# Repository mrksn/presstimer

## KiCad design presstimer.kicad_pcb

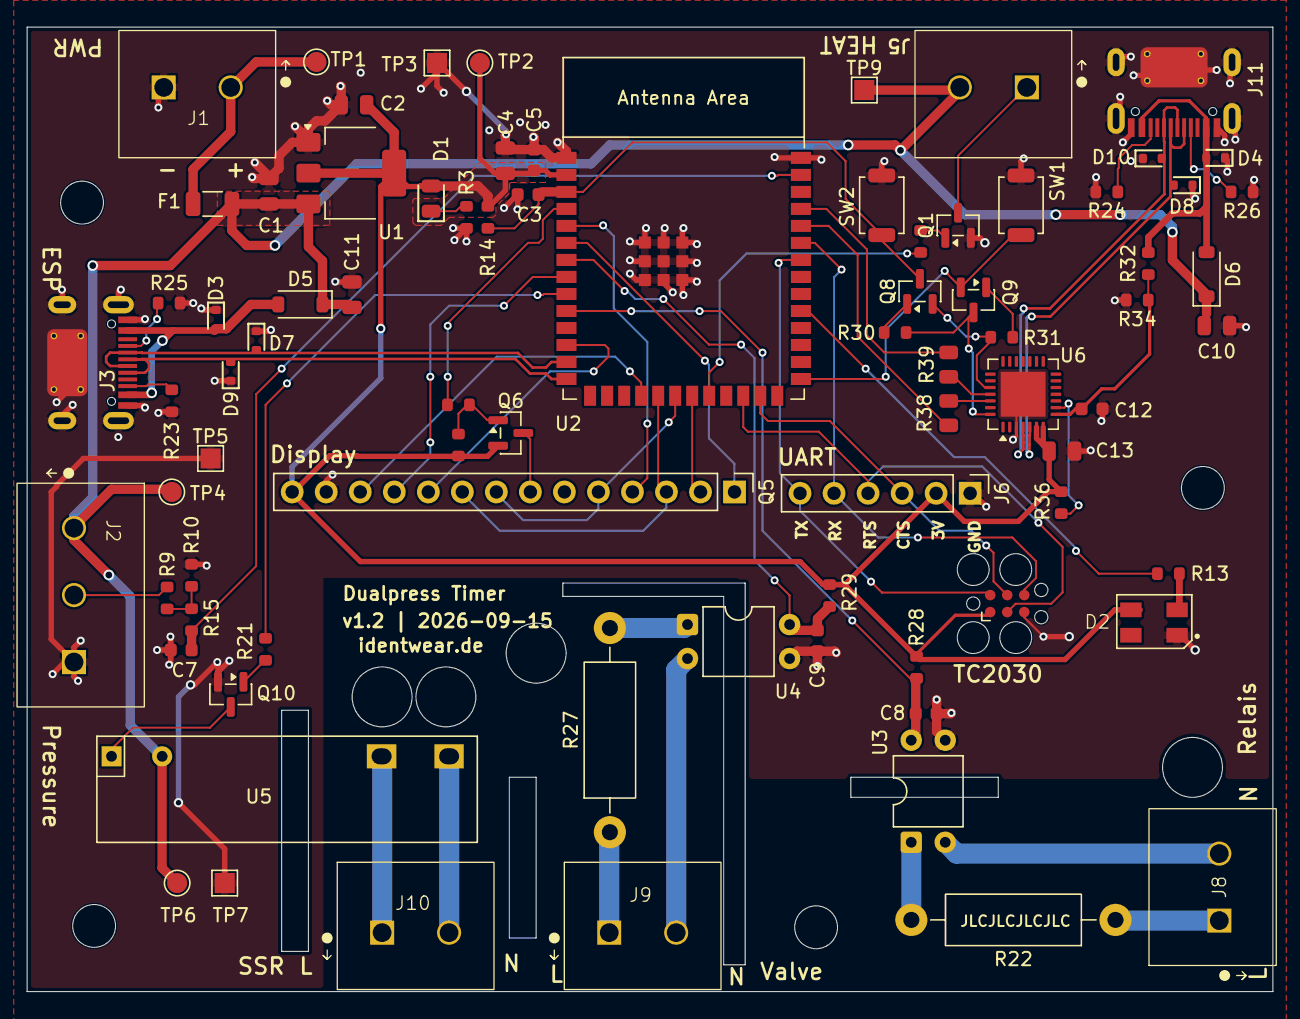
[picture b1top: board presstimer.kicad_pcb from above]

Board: 4 copper layers, 93.0 x 72.0 mm, 84 parts (0 on the bottom side), 63 nets.

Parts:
C1, C2: 1uF; C_0805
C3, C12: 1uF; C_0603
C4, C13: 10uF; C_0805
C5, C7, C8, C9: 100nF; C_0603
C10, C11: 22uF; C_0805
D1: LED; D_0805
D2: SK6812MINI; SK6812MINI--HS-012_3.7x3.5mm
D3, D4, D7, D8, D9, D10: LESD5D5.0CT1G; D_SOD-523
D5, D6: 1N5819HW-7-F; D_SOD-123
F1: Polyfuse; 1206L300SL16ARG
H1, H2, H3, H4: MountingHole; MountingHole_3.2mm_M3
J1, J5, J8, J9, J10: Screw_Terminal_01x02; DG305-5.0-02P-12-00A(H)
J2: Screw_Terminal_01x03; DG305-5.0-03P-12-00A(H)
J3, J11: Connector, USB-TYPE-C-16P; TYPE-C-SMD_HX-TYPE-C-16PIN
J4: Conn_ARM_SWD_TagConnect_TC2030; Tag-Connect_TC2030-IDC-FP_2x03_P1.27mm_Vertical
J6: Conn_01x06_Pin; PinHeader_1x06_P2.54mm_Vertical
Q1, Q8, Q9, Q10: L8050QLT1G; SOT-23
Q5: Display 2.8" TFT LCD Touch ILI9431 SPI; PinHeader_1x14_P2.54mm_Vertical
Q6: AO3401A; SOT-23
R1, R3, R15, R21, R36: 1k; R_0603
R9, R14, R30, R31: 10k; R_0603
R10: 15k; R_0603
R13: 330; R_0603
R16: 100; R_0603
R17: 100k; R_0603
R22, R27: 300k; R_Axial_DIN0411_L9.9mm_D3.6mm_P15.24mm_Horizontal
R23, R24, R25, R26: 5k1; R_0603
R28, R29: 47k; R_0603
R32: 22k1; R_0603
R34: 47k5; R_0603
R38, R39: 0; R_0805
SW1, SW2: SW_Push; SW_SPST_TS-1088-xR025
TP1, TP2, TP4, TP6: TestPoint; TestPoint_Pad_D1.5mm
TP3, TP5, TP7, TP9: TestPoint; TestPoint_Pad_1.5x1.5mm
U1: AP7361C-33ER; SOT-223R
U2: ESP32-S3-WROOM-1
U3, U4: SFH620A-3X001; DIP-4_W7.62mm
U5: SSR-41FDA; SSR-41FDD
U6: CP2102N-Axx-xQFN28; QFN-28-1EP_5x5mm_P0.5mm_EP3.35x3.35mm

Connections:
+3V3: C2.1, C4.1, C5.1, C13.1, D1.2 (A), D2.3 (VDD), J4.1 (VCC), J6.2, Q5.14 (VCC), Q6.2 (S), R14.2, R17.1, R28.1, R29.1, R36.1, TP2.1 (1_1), U1.2 (OUT), U1.4 (OUT), U2.2 (3V3), U6.6 (VDD), U6.7 (VREGIN)
+5V: C1.1, C10.1, C11.1, D5.1 (K), D6.1 (K), F1.2, J2.1, J5.2, TP4.1 (1_1), TP6.1 (1_1), TP9.1 (1_1), U1.3 (IN), U5.3 (+)
/Connections/SENSE_RELAY1: J8.1, R22.1
/Connections/SENSE_RELAY2: J8.2, U3.2
/Connections/SENSE_SOLENOID1: J9.1, R27.1
/Connections/SENSE_SOLENOID2: J9.2, U4.2
/Connections/SSR_L: J10.1, U5.2
/Connections/SSR_SW_L: J10.2, U5.1
BOOT: Q9.2 (E), SW1.1, U2.27 (GPIO0/BOOT/STRAP)
CHIP_PU: C3.1, Q8.3 (C), R14.1, SW2.1, U2.3 (EN)
DTR: Q9.3 (C), R30.1, U6.28 (~DTR)
D_BL: R16.1, U2.4 (GPIO4)
D_CS: Q5.12 (CS), U2.18 (GPIO10)
D_DC: Q5.10 (DC), U2.12 (GPIO8)
D_RST: Q5.11 (RESET), U2.8 (GPIO15)
D_SCK_T_CLK: Q5.5 (T_CLK), Q5.8 (SCK), U2.20 (GPIO12)
D_SDI_T_DIN: Q5.3 (T_DIN), Q5.9 (SDI), U2.19 (GPIO11)
D_T_CS: Q5.4 (T_CS), U2.5 (GPIO5)
D_T_DO: Q5.2 (T_DO), U2.21 (GPIO13)
D_T_IRQ: Q5.1 (T_IRQ), U2.6 (GPIO6)
GND: C1.2, C2.2, C3.2, C4.2, C5.2, C7.2, C8.2, C9.2, C10.2, C11.2, C12.2, C13.2, D2.1 (GND), D3.1 (A1), D4.1 (A1), D7.1 (A1), D8.1 (A1), D9.1 (A1), D10.1 (A1), J1.2, J2.3, J3.A12B1 (GND), J3.B12A1 (GND), J3.S1 (SHIELD), J4.5 (GND), J6.1, J11.A12B1 (GND), J11.B12A1 (GND), J11.S1 (SHIELD), Q1.2 (E), Q5.13 (GND), Q10.2 (E), R3.2, R10.2, R23.2, R24.2, R25.2, R26.2, R34.2, SW1.2, SW2.2, TP3.1 (1_1), TP5.1 (1_1), TP7.1 (1_1), U1.1 (GND), U2.1 (GND), U2.40 (GND), U2.41 (GND), U3.3, U4.3, U6.3 (GND), U6.29 (GND)
GPIO14: R1.1, U2.22 (GPIO14)
LED_RGB: R13.1, U2.31 (GPIO38)
unnamed: D1.1 (K), R3.1
unnamed: D2.2 (DIN), R13.2
unnamed: F1.1, J1.1, TP1.1 (1_1)
unnamed: J2.2, R9.2
unnamed: J3.A5 (CC1), R25.1
unnamed: J3.B5 (CC2), R23.1
unnamed: J5.1, Q1.3 (C)
unnamed: J11.A5 (CC1), R26.1
unnamed: J11.B5 (CC2), R24.1
unnamed: Q1.1 (B), R1.2
unnamed: Q5.7 (LED), Q6.3 (D)
unnamed: Q6.1 (G), R16.2, R17.2
unnamed: Q8.1 (B), R30.2
unnamed: Q9.1 (B), R31.2
unnamed: Q10.1 (B), R21.2
unnamed: Q10.3 (C), U5.4 (GND)
unnamed: R9.1, R10.1, R15.2
unnamed: R22.2, U3.1
unnamed: R27.2, U4.1
unnamed: R39.1, U6.25 (RXD)
unnamed: R38.1, U6.26 (TXD)
unnamed: C12.1, R32.2, R34.1, U6.8 (VBUS)
unnamed: R36.2, U6.9 (~RST)
RTS: Q8.2 (E), R31.1, U6.24 (~RTS)
SENSE_PRESSURE: C7.1, R15.1, U2.39 (GPIO1)
SENSE_RELAIS: C8.1, R28.2, U2.10 (GPIO17), U3.4
SENSE_VALVE: C9.1, R29.2, U2.7 (GPIO7), U4.4
SW_SSR: R21.1, U2.9 (GPIO16)
U0RXD: R38.2, U2.36 (U0RXD/GPIO44)
U0TXD: R39.2, U2.37 (U0TXD/GPIO43)
UART_CTS: J4.4 (SWCLK), J6.3, U2.25 (GPIO48)
UART_RTS: J4.3 (~RESET), J6.4, U2.24 (GPIO47)
UART_RX: J4.6 (SWO), J6.5, U2.35 (MTMS/GPIO42)
UART_TX: J4.2 (SWDIO), J6.6, U2.34 (MTDI/GPIO41)
USB2_DN: D8.2 (A2), J11.A7 (D-), J11.B7 (D-), U6.5 (D-)
USB2_DP: D10.2 (A2), J11.A6 (D+), J11.B6 (D+), U6.4 (D+)
USB_ESP_DN: D7.2 (A2), J3.A7 (D-), J3.B7 (D-), U2.13 (GPIO19/USB_D-)
USB_ESP_DP: D9.2 (A2), J3.A6 (D+), J3.B6 (D+), U2.14 (GPIO20/USB_D+)
VBUSB: D3.2 (A2), D5.2 (A), J3.A9B4 (VBUS), J3.B9A4 (VBUS)
VBUSB2: D4.2 (A2), D6.2 (A), J11.A9B4 (VBUS), J11.B9A4 (VBUS), R32.1

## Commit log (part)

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2026-06-19 schematic done
2026-06-19 footprints added, pcb started
2026-06-19 usb-uart added to schematic
2026-06-20 added usb-serial programmer and footprints
2026-06-21 before removing footprints
2026-06-21 before restore, crashed session
2026-06-21 parts assigned, footprints checked
2026-06-21 started pcb layout
2026-06-22 pcb layout v0.0.2
2026-06-22 pcb layout v0.0.3 (i forgot the second signal layer ;(.
2026-06-22 start over routing
2026-06-22 routing finished v0.1.0
2026-06-23 board finished v1.0
2026-06-26 html bom created
